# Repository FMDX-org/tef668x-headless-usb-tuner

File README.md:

# TEF668X Headless USB Tuner

USB radio tuner based on STM32F072 MCU and TEF6687 RF receiver with three antenna inputs and digital audio.

Copyright (C) 2024 FMDX.org

You may redistribute and modify this source under the terms of the CERN-OHL-W v2 (see LICENSE file).

# Credits 

- Konrad Kosmatka - HW & FW architecture and development
- Sjef Verhoeven - HW development
- Marek Kraus - HW & FW prototyping
- Marek Farkaš - testing and integration with FM-DX Webserver
- Przemysław Korpas - HW consultation, reviews
- Sebastian Białkowski - HW consultation, reviews

# Firmware

The firmware is available in a separate repository: [FM-DX-Tuner](https://github.com/kkonradpl/FM-DX-Tuner).

Firmware dependencies:
- Board: STM32 MCU Based Boards ([STM32duino](https://github.com/stm32duino)) - download using board manager
- Library: [TinyUSB](https://github.com/hathach/tinyusb) - install manually to the Arduino libraries

During first firmware flashing, short BOOT to 3.3V, plug the USB cable and flash using Arduino IDE (DFU method). Once the firmware is running, it is not necessary to manually short BOOT pin. See [tef-bootloader](https://github.com/kkonradpl/tef-bootloader).

# Audio output

The baseline version of the tuner supports only digital audio over USB. For a regular analog audio line-out, see the [Audiohat for Headless TEF](https://github.com/PE5PVB/Audiohat-Headless-TEF/).

# Important remarks

- TEF6687/V205 (F8705) chip is recommended for the best performance (FMSI, FULL SCAN RDS).
- RF circuits should contain NP0 (C0G) capacitors.
- Only V205 version of TEF668X supports the 55.46667 MHz crystal.
- For a crystal different than 55.46667 MHz, GPIO1 must be pulled to the ground (instead of pull-up).
- All capacitors and resistors are 0603, except R30 and R31 which are 0402.

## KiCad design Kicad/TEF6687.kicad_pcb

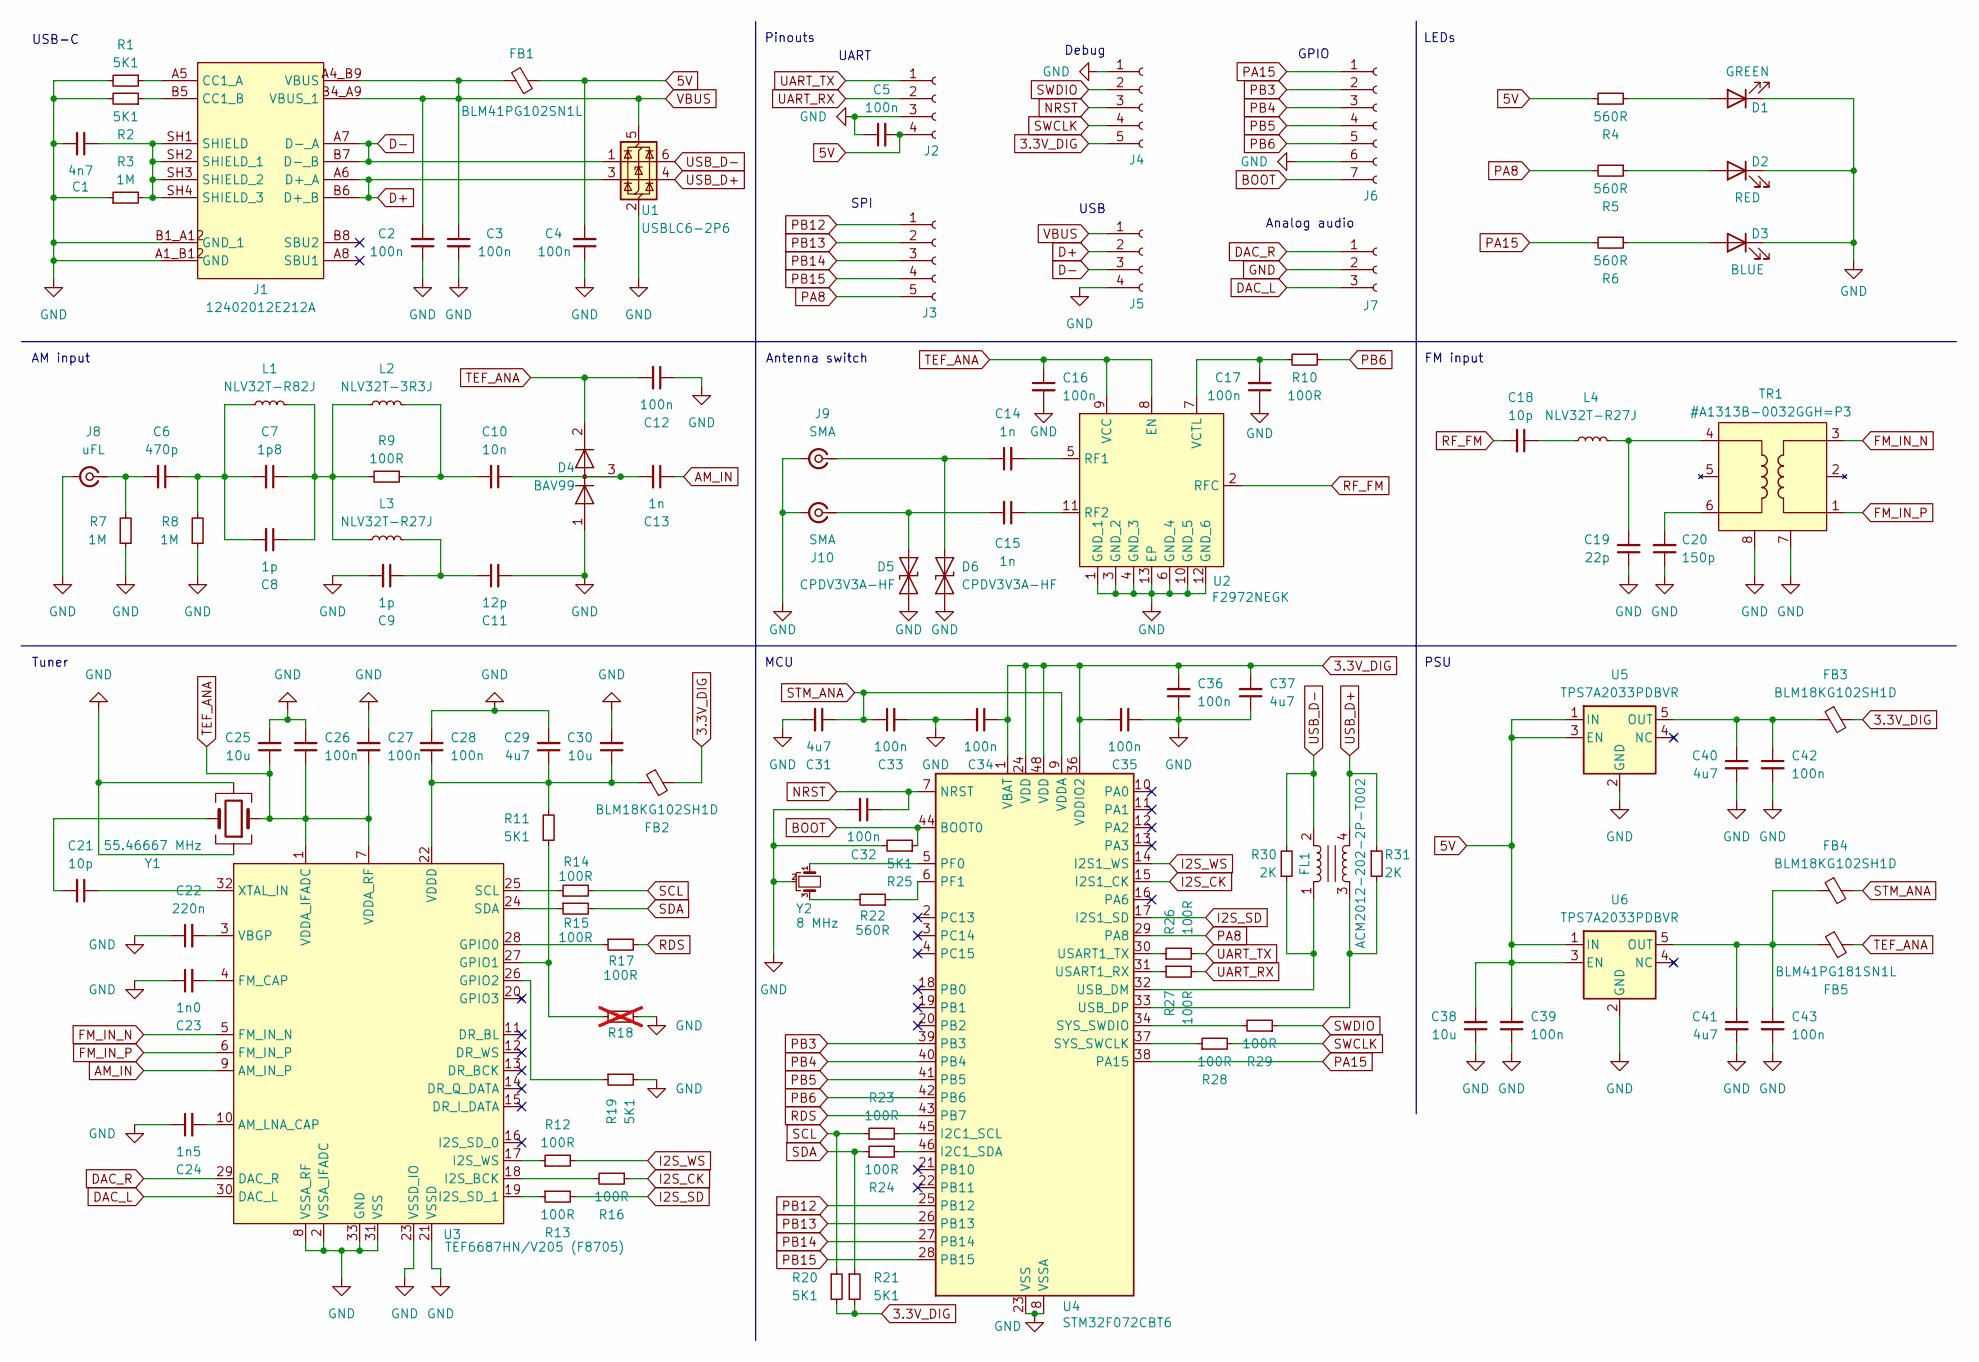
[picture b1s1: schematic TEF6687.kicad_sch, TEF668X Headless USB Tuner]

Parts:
C1: 4n7; C_0603_1608Metric
C2, C3, C4, C5, C12, C16, C17, C26, C27, C28, C32, C33, C34, C35, C36, C39, C42, C43: 100n; C_0603_1608Metric
C6: 470p; C_0603_1608Metric
C7: 1p8; C_0603_1608Metric
C8, C9: 1p; C_0603_1608Metric
C10: 10n; C_0603_1608Metric
C11: 12p; C_0603_1608Metric
C13, C14, C15: 1n; C_0603_1608Metric
C18, C21: 10p; C_0603_1608Metric
C19: 22p; C_0603_1608Metric
C20: 150p; C_0603_1608Metric
C22: 220n; C_0603_1608Metric
C23: 1n0; C_0603_1608Metric
C24: 1n5; C_0603_1608Metric
C25, C30, C38: 10u; C_0603_1608Metric
C29, C31, C37, C40, C41: 4u7; C_0603_1608Metric
D1: GREEN; LED_D1.8mm_W3.3mm_H2.4mm
D2: RED; LED_D1.8mm_W3.3mm_H2.4mm
D3: BLUE; LED_D1.8mm_W3.3mm_H2.4mm
D4: BAV99; SOT-23
D5, D6: CPDV3V3A-HF; D_SOD-323_HandSoldering
FB1: BLM41PG102SN1L; L_1806_4516Metric
FB2, FB3, FB4: BLM18KG102SH1D; L_0603_1608Metric
FB5: BLM41PG181SN1L; L_1806_4516Metric
FL1: ACM2012-202-2P-T002; USB_Filter_0805
J1: 12402012E212A
J2: 1x4; PinSocket_1x04_P2.54mm_Vertical
J3, J4: 1x5; PinSocket_1x05_P2.54mm_Vertical
J5: 1x4; JST_PH_S4B-PH-SM4-TB_1x04-1MP_P2.00mm_Horizontal
J6: 1x7; PinSocket_1x07_P2.54mm_Vertical
J7: 1x3; PinSocket_1x03_P2.54mm_Vertical
J8: uFL; U.FL_Molex_MCRF_73412-0110_Vertical
J9, J10: SMA; SMA_Molex_73251-2120_EdgeMount_Horizontal
L1: NLV32T-R82J; L_TDK_NLV32_3.2x2.5mm
L2: NLV32T-3R3J; L_TDK_NLV32_3.2x2.5mm
L3, L4: NLV32T-R27J; L_TDK_NLV32_3.2x2.5mm
R1, R2, R11, R19, R20, R21, R25: 5K1; R_0603_1608Metric
R3, R7, R8: 1M; R_0603_1608Metric
R4, R5, R6, R22: 560R; R_0603_1608Metric
R9, R10, R12, R13, R14, R15, R16, R17, R23, R24, R26, R27, R28, R29: 100R; R_0603_1608Metric
R18: 5K1 (only place when other crystal is used!); R_0603_1608Metric; not fitted
R30, R31: 2K; R_0402_1005Metric
TR1: #A1313B-0032GGH=P3; RF_Transformer
U1: USBLC6-2P6; SOT-666
U2: F2972NEGK; QFN_RF_Switch
U3: TEF6687HN/V205 (F8705); TEF668x
U4: STM32F072CBT6; LQFP-48_7x7mm_P0.5mm
U5, U6: TPS7A2033PDBVR; SOT-23-5
Y1: 55.46667 MHz; Crystal_SMD_3225-4Pin_3.2x2.5mm
Y2: 8 MHz; Resonator_SMD_Murata_CSTxExxV-3Pin_3.0x1.1mm

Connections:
3.3V_DIG: C34.1, C35.2, C36.2, C37.2, FB2.1, FB3.2, J4.5, R20.2, R21.2, U4.1 (VBAT), U4.24 (VDD), U4.36 (VDDIO2), U4.48 (VDD)
5V: C4.2, C5.2, C38.2, C39.2, FB1.1, J2.4, R4.1, U5.1 (IN), U5.3 (EN), U6.1 (IN), U6.3 (EN)
AM_IN: C13.1, U3.9 (AM_IN_P)
BOOT: J6.7, R25.1, U4.44 (BOOT0)
D+: J1.A6 (D+_A), J1.B6 (D+_B), J5.2, U1.3 (I/O2)
D-: J1.A7 (D-_A), J1.B7 (D-_B), J5.3, U1.1 (I/O1)
DAC_L: J7.3, U3.30 (DAC_L)
DAC_R: J7.1, U3.29 (DAC_R)
FM_IN_N: TR1.3, U3.5 (FM_IN_N)
FM_IN_P: TR1.1, U3.6 (FM_IN_P)
GND: C1.2, C2.1, C3.2, C4.1, C5.1, C9.2, C11.2, C12.1, C16.2, C17.1, C19.1, C20.1, C22.1, C23.1, C24.1, C25.2, C26.2, C27.2, C28.2, C29.2, C30.2, C31.2, C32.2, C33.2, C34.2, C35.1, C36.1, C37.1, C38.1, C39.1, C40.2, C41.2, C42.2, C43.2, D1.1 (K), D2.1 (K), D3.1 (K), D4.1 (K), D5.2 (A2), D6.2 (A2), J1.A1_B12 (GND), J1.B1_A12 (GND_1), J2.3, J4.1, J5.4, J6.6, J7.2, J8.2 (Ext), J9.2 (Ext), J10.2 (Ext), R1.2, R2.2, R3.1, R7.1, R8.1, R18.2, R19.2, R25.2, TR1.7, TR1.8, U1.2 (GND), U2.1 (GND_1), U2.3 (GND_2), U2.4 (GND_3), U2.6 (GND_4), U2.10 (GND_5), U2.12 (GND_6), U2.13 (EP), U3.2 (VSSA_IFADC), U3.8 (VSSA_RF), U3.21 (VSSD), U3.23 (VSSD_IO), U3.31 (VSS), U3.33 (GND), U4.8 (VSSA), U4.23 (VSS), U4.35 (VSS), U4.47 (VSS), U5.2 (GND), U6.2 (GND), Y1.2, Y1.4, Y2.2
I2S_CK: R16.1, U4.15 (I2S1_CK)
I2S_SD: R13.2, U4.17 (I2S1_SD)
I2S_WS: R12.2, U4.14 (I2S1_WS)
NRST: C32.1, J4.3, U4.7 (NRST)
unnamed: C6.1, C7.2, C8.2, L1.1, R8.2
unnamed: C7.1, C8.1, L1.2, L2.1, L3.1, R9.2
unnamed: C10.1, C13.2, D4.3 (K)
unnamed: C10.2, L2.2, R9.1
unnamed: C9.1, C11.1, L3.2
unnamed: C18.1, L4.1
unnamed: C19.2, L4.2, TR1.4
unnamed: C20.2, TR1.6
unnamed: C21.2, Y1.3
unnamed: D1.2 (A), R4.2
unnamed: D2.2 (A), R5.1
unnamed: D3.2 (A), R6.1
unnamed: C15.2, D5.1 (A1), J10.1 (In)
unnamed: C14.1, D6.1 (A1), J9.1 (In)
unnamed: J1.A5 (CC1_A), R1.1
unnamed: J1.B5 (CC1_B), R2.1
unnamed: C1.1, J1.SH1 (SHIELD), J1.SH2 (SHIELD_1), J1.SH3 (SHIELD_2), J1.SH4 (SHIELD_3), R3.2
unnamed: C6.2, J8.1 (In), R7.2
unnamed: R22.2, Y2.3
unnamed: C14.2, U2.5 (RF1)
unnamed: C15.1, U2.11 (RF2)
unnamed: C17.2, R10.2, U2.7 (VCTL)
unnamed: C24.2, U3.10 (AM_LNA_CAP)
unnamed: C23.2, U3.4 (FM_CAP)
unnamed: R17.1, U3.28 (GPIO0)
unnamed: R11.1, R18.1, U3.27 (GPIO1)
unnamed: R19.1, U3.26 (GPIO2)
unnamed: R16.2, U3.18 (I2S_BCK)
unnamed: R13.1, U3.19 (I2S_SD_1)
unnamed: R12.1, U3.17 (I2S_WS)
unnamed: R14.1, U3.25 (SCL)
unnamed: R15.1, U3.24 (SDA)
unnamed: C22.2, U3.3 (VBGP)
unnamed: C28.1, C29.1, C30.1, FB2.2, R11.2, U3.22 (VDDD)
unnamed: C21.1, U3.32 (XTAL_IN)
unnamed: R26.1, U4.30 (USART1_TX)
unnamed: R27.1, U4.31 (USART1_RX)
unnamed: FL1.1, R30.1, U4.32 (USB_DM)
unnamed: FL1.3, R31.2, U4.33 (USB_DP)
unnamed: R29.2, U4.34 (SYS_SWDIO)
unnamed: R28.1, U4.37 (SYS_SWCLK)
unnamed: R23.2, U4.45 (I2C1_SCL)
unnamed: R24.2, U4.46 (I2C1_SDA)
unnamed: U4.5 (PF0), Y2.1
unnamed: R22.1, U4.6 (PF1)
unnamed: C40.1, C42.1, FB3.1, U5.5 (OUT)
unnamed: C41.1, C43.1, FB4.1, FB5.2, U6.5 (OUT)
PA8: J3.5, R5.2, U4.29 (PA8)
PA15: J6.1, R6.2, U4.38 (PA15)
PB3: J6.2, U4.39 (PB3)
PB4: J6.3, U4.40 (PB4)
PB5: J6.4, U4.41 (PB5)
PB6: J6.5, R10.1, U4.42 (PB6)
PB12: J3.1, U4.25 (PB12)
PB13: J3.2, U4.26 (PB13)
PB14: J3.3, U4.27 (PB14)
PB15: J3.4, U4.28 (PB15)
RDS: R17.2, U4.43 (PB7)
RF_FM: C18.2, U2.2 (RFC)
SCL: R14.2, R20.1, R23.1
SDA: R15.2, R21.1, R24.1
STM_ANA: C31.1, C33.1, FB4.2, U4.9 (VDDA)
SWCLK: J4.4, R28.2
SWDIO: J4.2, R29.1
TEF_ANA: C12.2, C16.1, C25.1, C26.1, C27.1, D4.2 (A), FB5.1, U2.8 (EN), U2.9 (VCC), U3.1 (VDDA_IFADC), U3.7 (VDDA_RF), Y1.1
UART_RX: J2.2, R27.2
UART_TX: J2.1, R26.2
USB_D+: FL1.4, R31.1, U1.4 (I/O2)
USB_D-: FL1.2, R30.2, U1.6 (I/O1)
VBUS: C2.2, C3.1, FB1.2, J1.A4_B9 (VBUS), J1.B4_A9 (VBUS_1), J5.1, U1.5 (VBUS)

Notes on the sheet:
PSU
Pinouts
USB
AM input
GPIO
Antenna switch
Analog audio
MCU
UART
Tuner
USB-C
Debug
FM input
SPI
LEDs

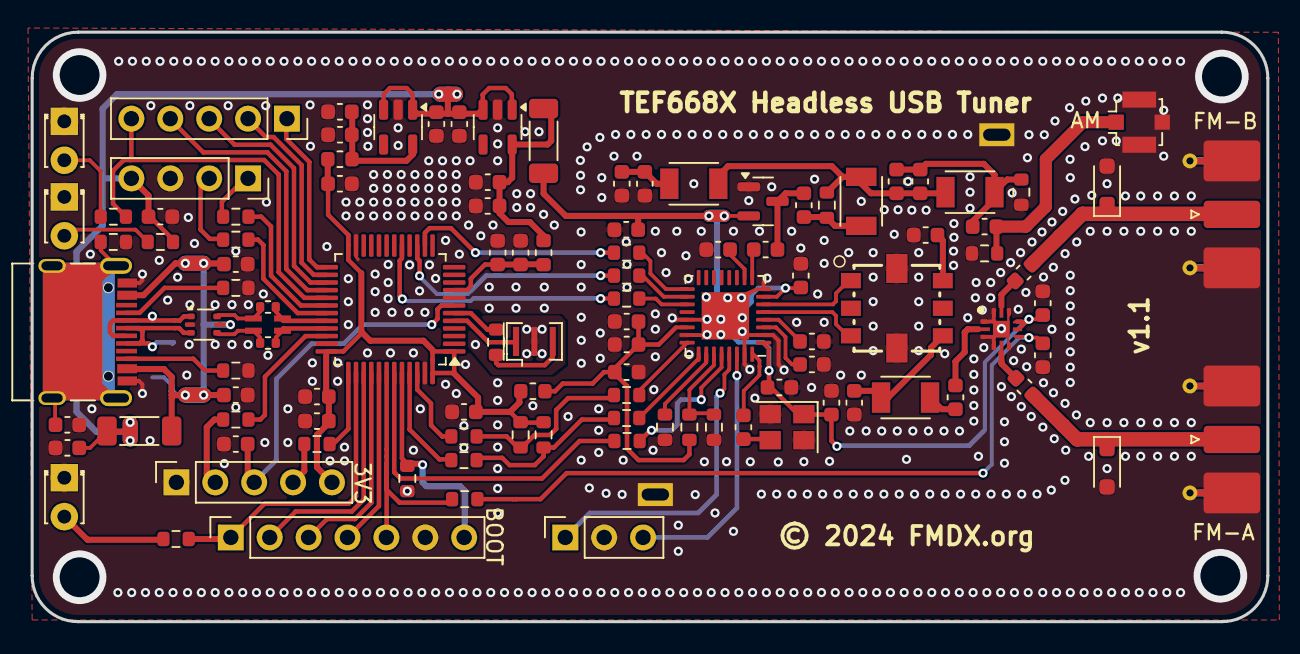
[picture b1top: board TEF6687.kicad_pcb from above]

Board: 2 copper layers, 80.7 x 38.5 mm, 109 parts (1 on the bottom side), 85 nets.

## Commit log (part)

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2024-09-07 Add schematics
2024-09-14 Final release
2024-09-14 Update README and add BOM
2024-11-17 Added gerbers
2024-11-17 Added 3d case
2025-01-20 Update 3d model to STL files

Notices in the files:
Kicad/TEF6687.kicad_pcb:
© 2024 FMDX.org
